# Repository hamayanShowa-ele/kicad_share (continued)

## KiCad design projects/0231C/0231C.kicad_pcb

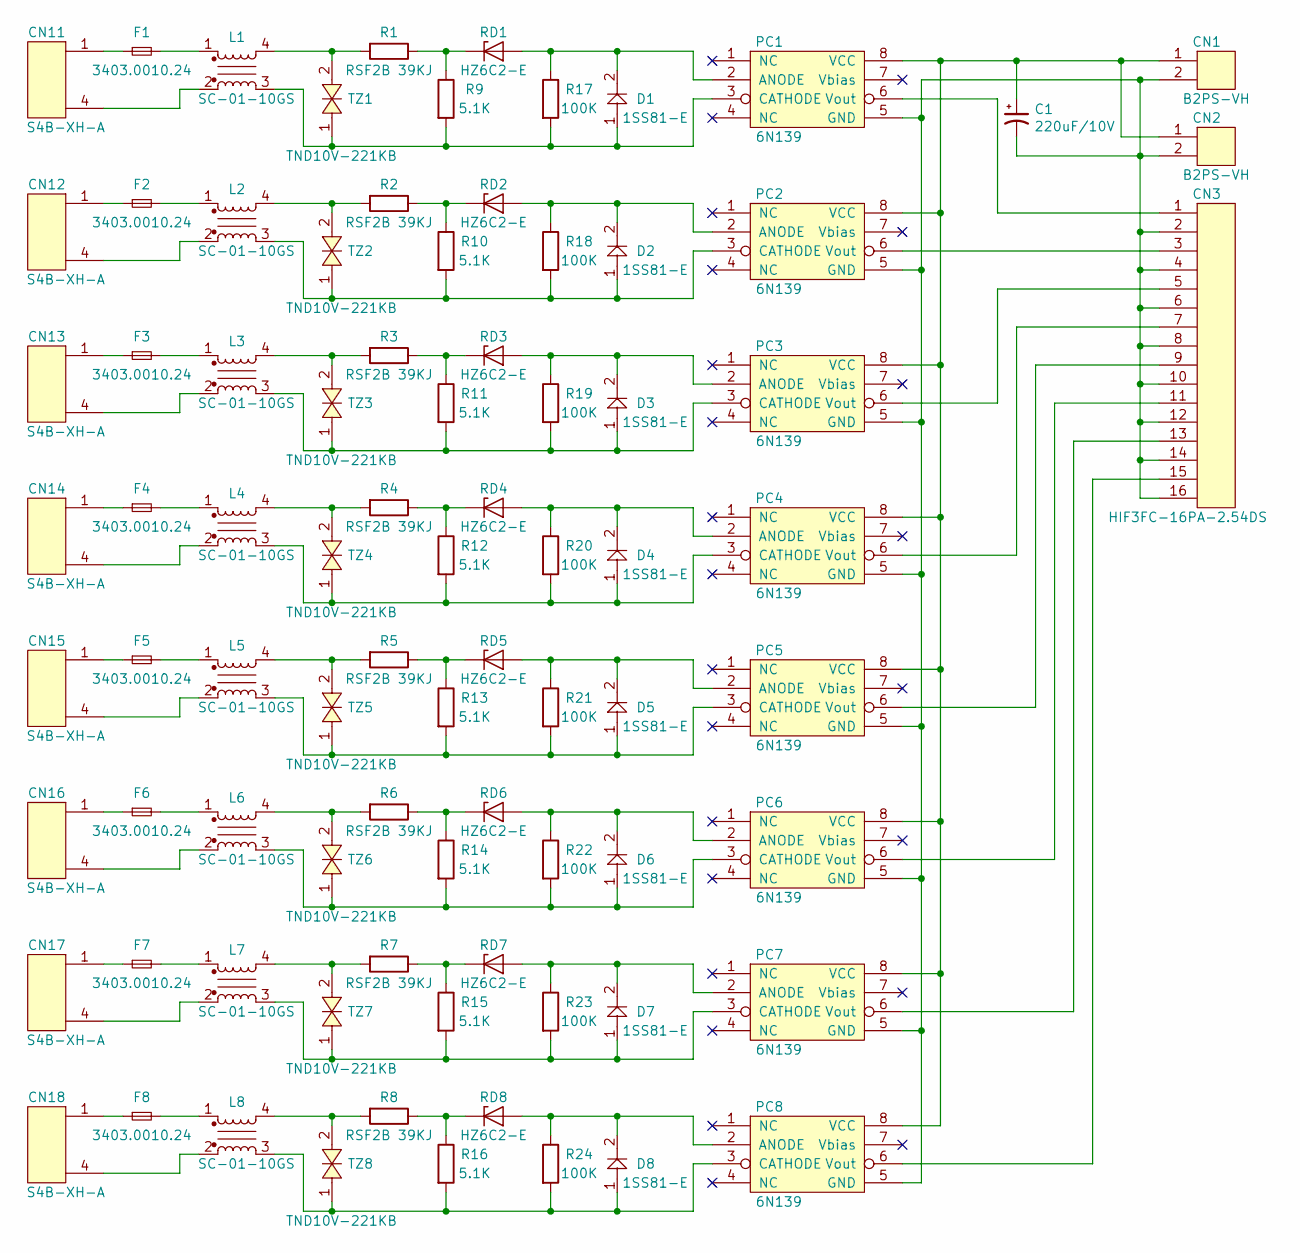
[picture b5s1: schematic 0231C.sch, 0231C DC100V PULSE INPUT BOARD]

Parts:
C1: 220uF/10V; CP_Radial_D8.00mm_P2.50mm
CN1, CN2: B2PS-VH; cn_B2PS-VH
CN3: HIF3FC-16PA-2.54DS; cn_HIF3FC-16PA-254DS
CN11, CN12, CN13, CN14, CN15, CN16, CN17, CN18: S4B-XH-A; cn_S4B-XH-A_KIRI_2-3
D1, D2, D3, D4, D5, D6, D7, D8: 1SS81-E; D_TH_10R16
F1, F2, F3, F4, F5, F6, F7, F8: 3403.0010.24; f_3403_0010_24
L1, L2, L3, L4, L5, L6, L7, L8: SC-01-10GS; l_SC-01-10GS
PC1, PC2, PC3, PC4, PC5, PC6, PC7, PC8: 6N139; ic_DIP-8_W7.62mm
R1, R2, R3, R4, R5, R6, R7, R8: RSF2B 39KJ; r_RSF2B
R9, R10, R11, R12, R13, R14, R15, R16: 5.1K; R_TH_10R16
R17, R18, R19, R20, R21, R22, R23, R24: 100K; R_TH_10R16
RD1, RD2, RD3, RD4, RD5, RD6, RD7, RD8: HZ6C2-E; RD_TH_10R16
TZ1, TZ2, TZ3, TZ4, TZ5, TZ6, TZ7, TZ8: TND10V-221KB; tvs_TND10V-221KB

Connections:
unnamed: C1.1, CN1.1, CN2.1, PC1.8 (VCC), PC2.8 (VCC), PC3.8 (VCC), PC4.8 (VCC), PC5.8 (VCC), PC6.8 (VCC), PC7.8 (VCC), PC8.8 (VCC)
unnamed: C1.2, CN1.2, CN2.2, CN3.2, CN3.4, CN3.6, CN3.8, CN3.10, CN3.12, CN3.14, CN3.16, PC1.5 (GND), PC2.5 (GND), PC3.5 (GND), PC4.5 (GND), PC5.5 (GND), PC6.5 (GND), PC7.5 (GND), PC8.5 (GND)
unnamed: CN3.1, PC1.6 (Vout)
unnamed: CN3.3, PC2.6 (Vout)
unnamed: CN3.5, PC3.6 (Vout)
unnamed: CN3.7, PC4.6 (Vout)
unnamed: CN3.9, PC5.6 (Vout)
unnamed: CN3.11, PC6.6 (Vout)
unnamed: CN3.13, PC7.6 (Vout)
unnamed: CN3.15, PC8.6 (Vout)
unnamed: CN11.1, F1.1
unnamed: CN11.4, L1.2
unnamed: CN12.1, F2.1
unnamed: CN12.4, L2.2
unnamed: CN13.1, F3.1
unnamed: CN13.4, L3.2
unnamed: CN14.1, F4.1
unnamed: CN14.4, L4.2
unnamed: CN15.1, F5.1
unnamed: CN15.4, L5.2
unnamed: CN16.1, F6.1
unnamed: CN16.4, L6.2
unnamed: CN17.1, F7.1
unnamed: CN17.4, L7.2
unnamed: CN18.1, F8.1
unnamed: CN18.4, L8.2
unnamed: D1.1, L1.3, PC1.3 (CATHODE), R9.2, R17.2, TZ1.1
unnamed: D1.2, PC1.2 (ANODE), R17.1, RD1.1 (A)
unnamed: D2.1, L2.3, PC2.3 (CATHODE), R10.2, R18.2, TZ2.1
unnamed: D2.2, PC2.2 (ANODE), R18.1, RD2.1 (A)
unnamed: D3.1, L3.3, PC3.3 (CATHODE), R11.2, R19.2, TZ3.1
unnamed: D3.2, PC3.2 (ANODE), R19.1, RD3.1 (A)
unnamed: D4.1, L4.3, PC4.3 (CATHODE), R12.2, R20.2, TZ4.1
unnamed: D4.2, PC4.2 (ANODE), R20.1, RD4.1 (A)
unnamed: D5.1, L5.3, PC5.3 (CATHODE), R13.2, R21.2, TZ5.1
unnamed: D5.2, PC5.2 (ANODE), R21.1, RD5.1 (A)
unnamed: D6.1, L6.3, PC6.3 (CATHODE), R14.2, R22.2, TZ6.1
unnamed: D6.2, PC6.2 (ANODE), R22.1, RD6.1 (A)
unnamed: D7.1, L7.3, PC7.3 (CATHODE), R15.2, R23.2, TZ7.1
unnamed: D7.2, PC7.2 (ANODE), R23.1, RD7.1 (A)
unnamed: D8.1, L8.3, PC8.3 (CATHODE), R16.2, R24.2, TZ8.1
unnamed: D8.2, PC8.2 (ANODE), R24.1, RD8.1 (A)
unnamed: F1.2, L1.1
unnamed: F2.2, L2.1
unnamed: F3.2, L3.1
unnamed: F4.2, L4.1
unnamed: F5.2, L5.1
unnamed: F6.2, L6.1
unnamed: F7.2, L7.1
unnamed: F8.2, L8.1
unnamed: L1.4, R1.2, TZ1.2
unnamed: L2.4, R2.2, TZ2.2
unnamed: L3.4, R3.2, TZ3.2
unnamed: L4.4, R4.2, TZ4.2
unnamed: L5.4, R5.2, TZ5.2
unnamed: L6.4, R6.2, TZ6.2
unnamed: L7.4, R7.2, TZ7.2
unnamed: L8.4, R8.2, TZ8.2
unnamed: R1.1, R9.1, RD1.2 (K)
unnamed: R2.1, R10.1, RD2.2 (K)
unnamed: R3.1, R11.1, RD3.2 (K)
unnamed: R4.1, R12.1, RD4.2 (K)
unnamed: R5.1, R13.1, RD5.2 (K)
unnamed: R6.1, R14.1, RD6.2 (K)
unnamed: R7.1, R15.1, RD7.2 (K)
unnamed: R8.1, R16.1, RD8.2 (K)

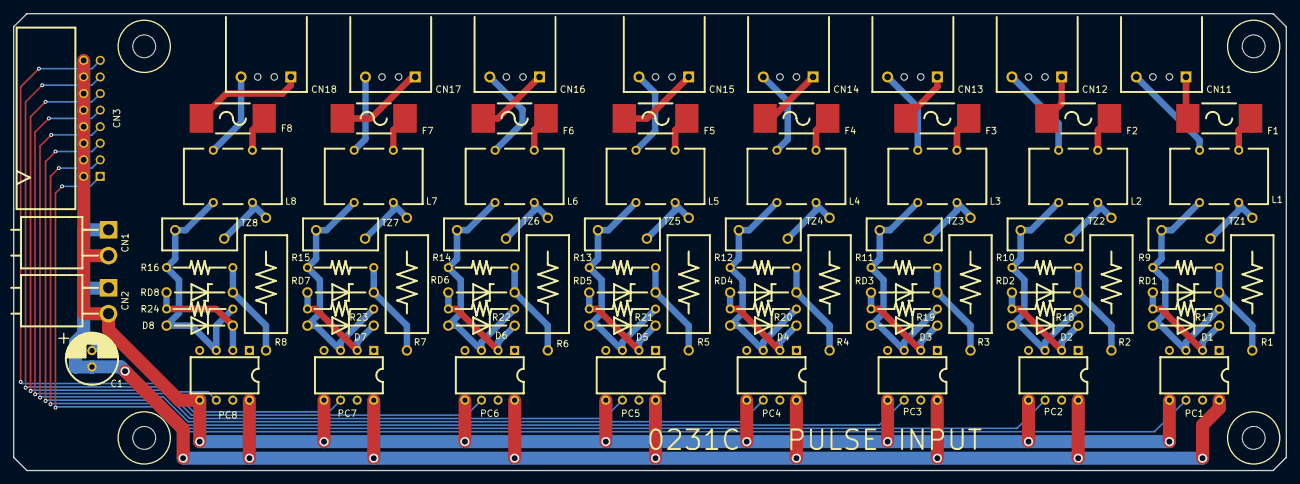
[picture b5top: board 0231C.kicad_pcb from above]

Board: 2 copper layers, 195.0 x 70.0 mm, 84 parts (0 on the bottom side), 66 nets.

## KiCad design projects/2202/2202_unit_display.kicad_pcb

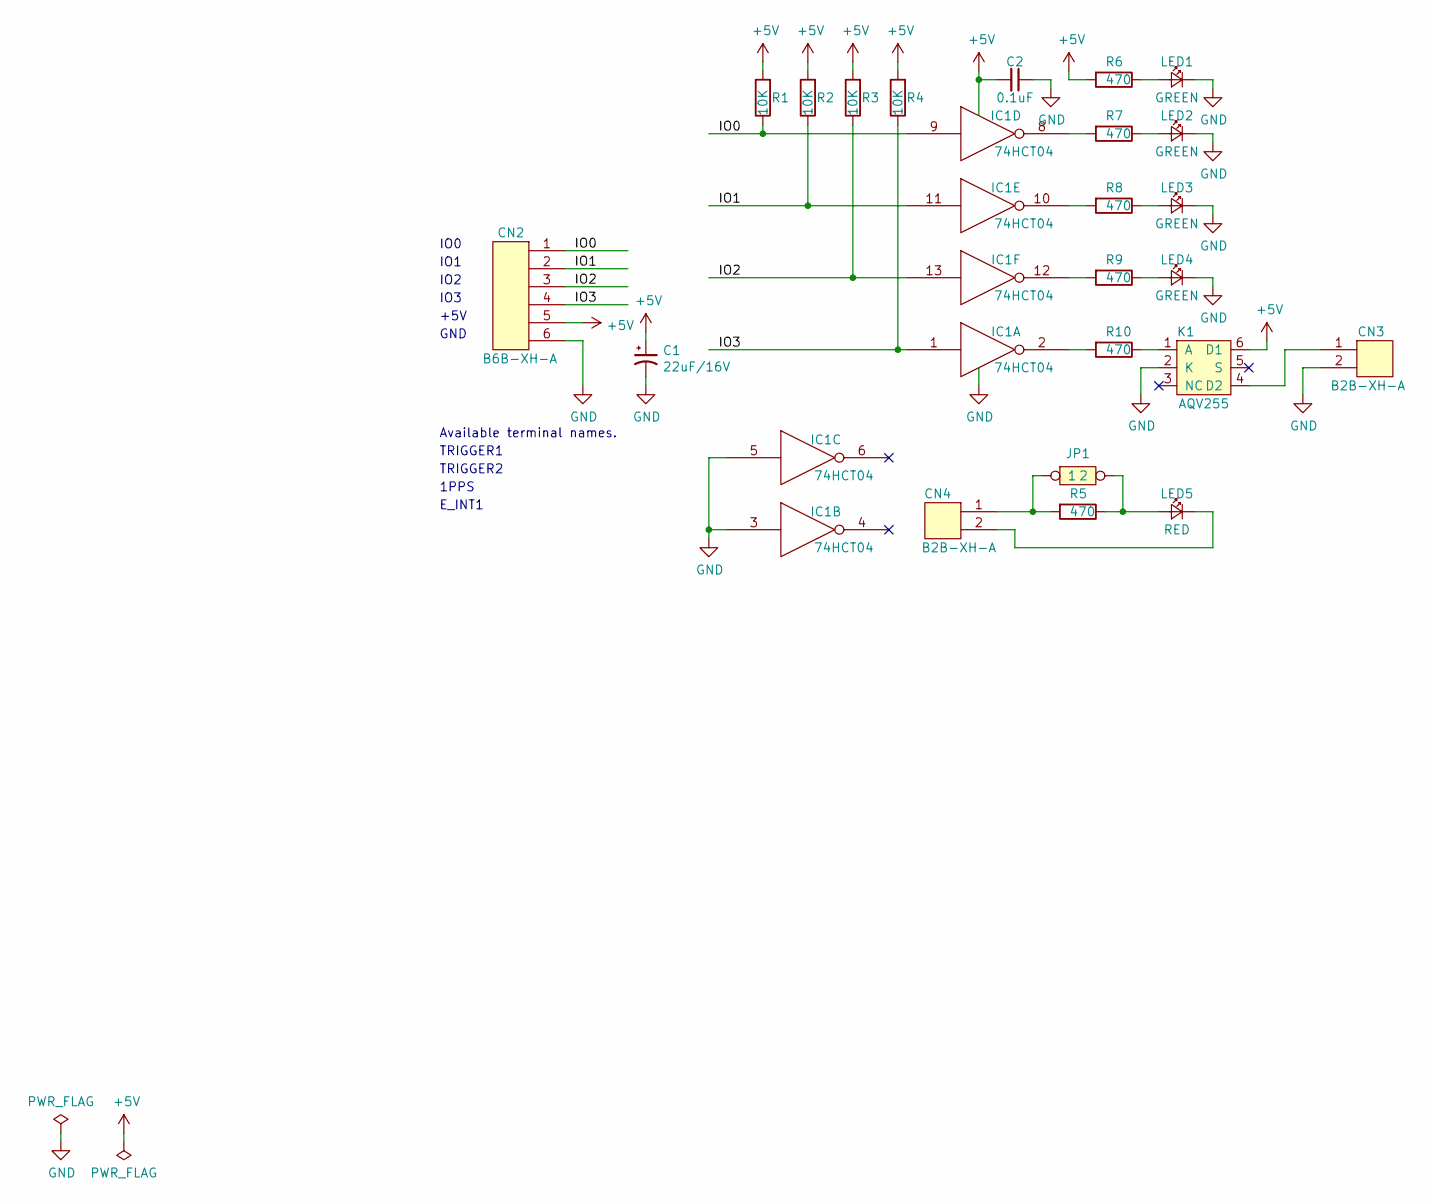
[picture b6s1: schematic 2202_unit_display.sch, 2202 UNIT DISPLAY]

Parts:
C1: 22uF/16V; CP_Radial_D5.0mm_P2.00mm
C2: 0.1uF; C_0603
CN2: B6B-XH-A; cn_B6B-XH-A
CN3, CN4: B2B-XH-A; cn_B2B-XH-A
IC1: 74HCT04; ic_DIP-14_W7.62mm
JP1: JUMPER2*1; JP_JUMPER1x2
K1: AQV255; ic_DIP-6_W7.62mm
LED1, LED2, LED3, LED4: GREEN; LED_D3.0mm_center
LED5: RED; LED_D3.0mm_center
R1, R2, R3, R4: 10K; R_TH_5R08
R5, R6, R7, R8, R9, R10: 470; R_TH_5R08

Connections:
+5V: C1.1, C2.2, CN2.5, IC1.14 (VCC), K1.6 (D1), R1.2, R2.2, R3.2, R4.2, R6.2
/IO0: CN2.1, IC1.9, R1.1
/IO1: CN2.2, IC1.11, R2.1
/IO2: CN2.3, IC1.13, R3.1
/IO3: CN2.4, IC1.1, R4.1
GND: C1.2, C2.1, CN2.6, CN3.2, IC1.3, IC1.5, IC1.7 (GNDA), K1.2 (K), LED1.2 (K), LED2.2 (K), LED3.2 (K), LED4.2 (K)
unnamed: CN3.1, K1.4 (D2)
unnamed: CN4.1, JP1.1, R5.2
unnamed: CN4.2, LED5.2 (K)
unnamed: IC1.2, R10.2
unnamed: IC1.8, R7.2
unnamed: IC1.10, R8.2
unnamed: IC1.12, R9.2
unnamed: JP1.2, LED5.1 (A), R5.1
unnamed: K1.1 (A), R10.1
unnamed: LED1.1 (A), R6.1
unnamed: LED2.1 (A), R7.1
unnamed: LED3.1 (A), R8.1
unnamed: LED4.1 (A), R9.1

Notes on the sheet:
TRIGGER1
TRIGGER2
1PPS
E_INT1
+5V
GND
IO0
IO1
IO2
IO3
Available terminal names.

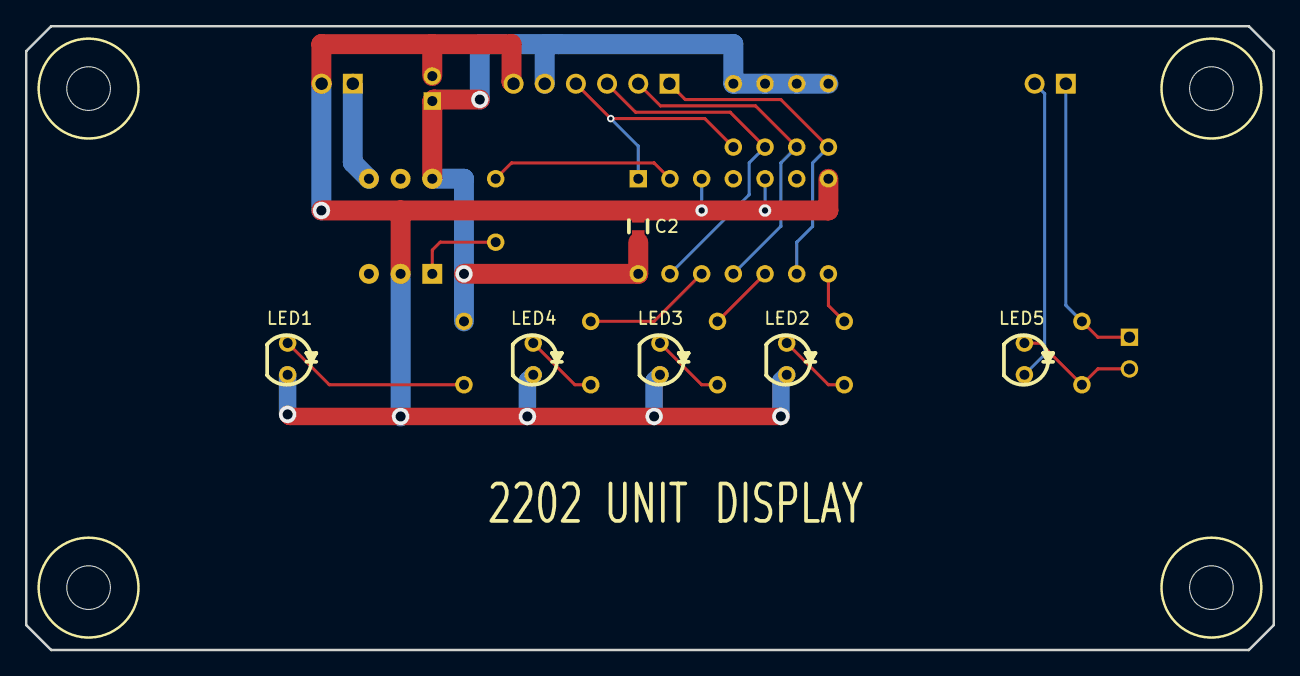
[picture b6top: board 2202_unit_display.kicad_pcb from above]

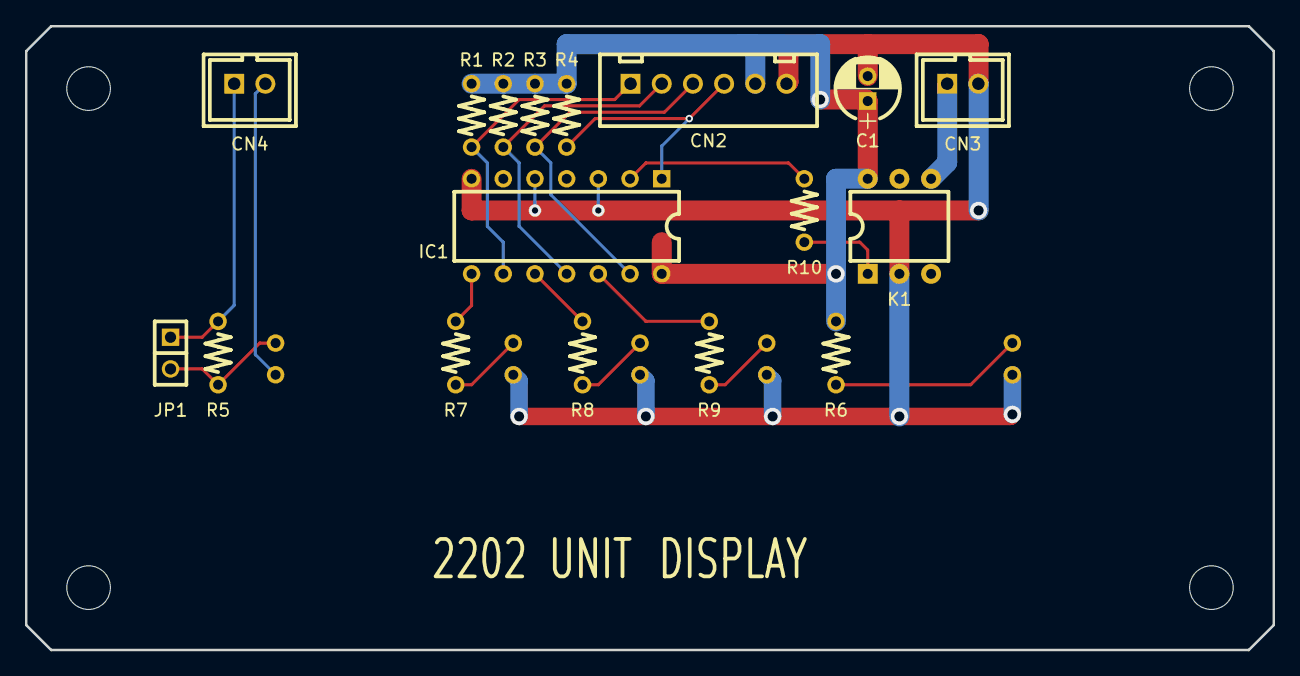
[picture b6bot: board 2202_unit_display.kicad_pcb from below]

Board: 2 copper layers, 100.0 x 50.0 mm, 23 parts (17 on the bottom side), 19 nets.

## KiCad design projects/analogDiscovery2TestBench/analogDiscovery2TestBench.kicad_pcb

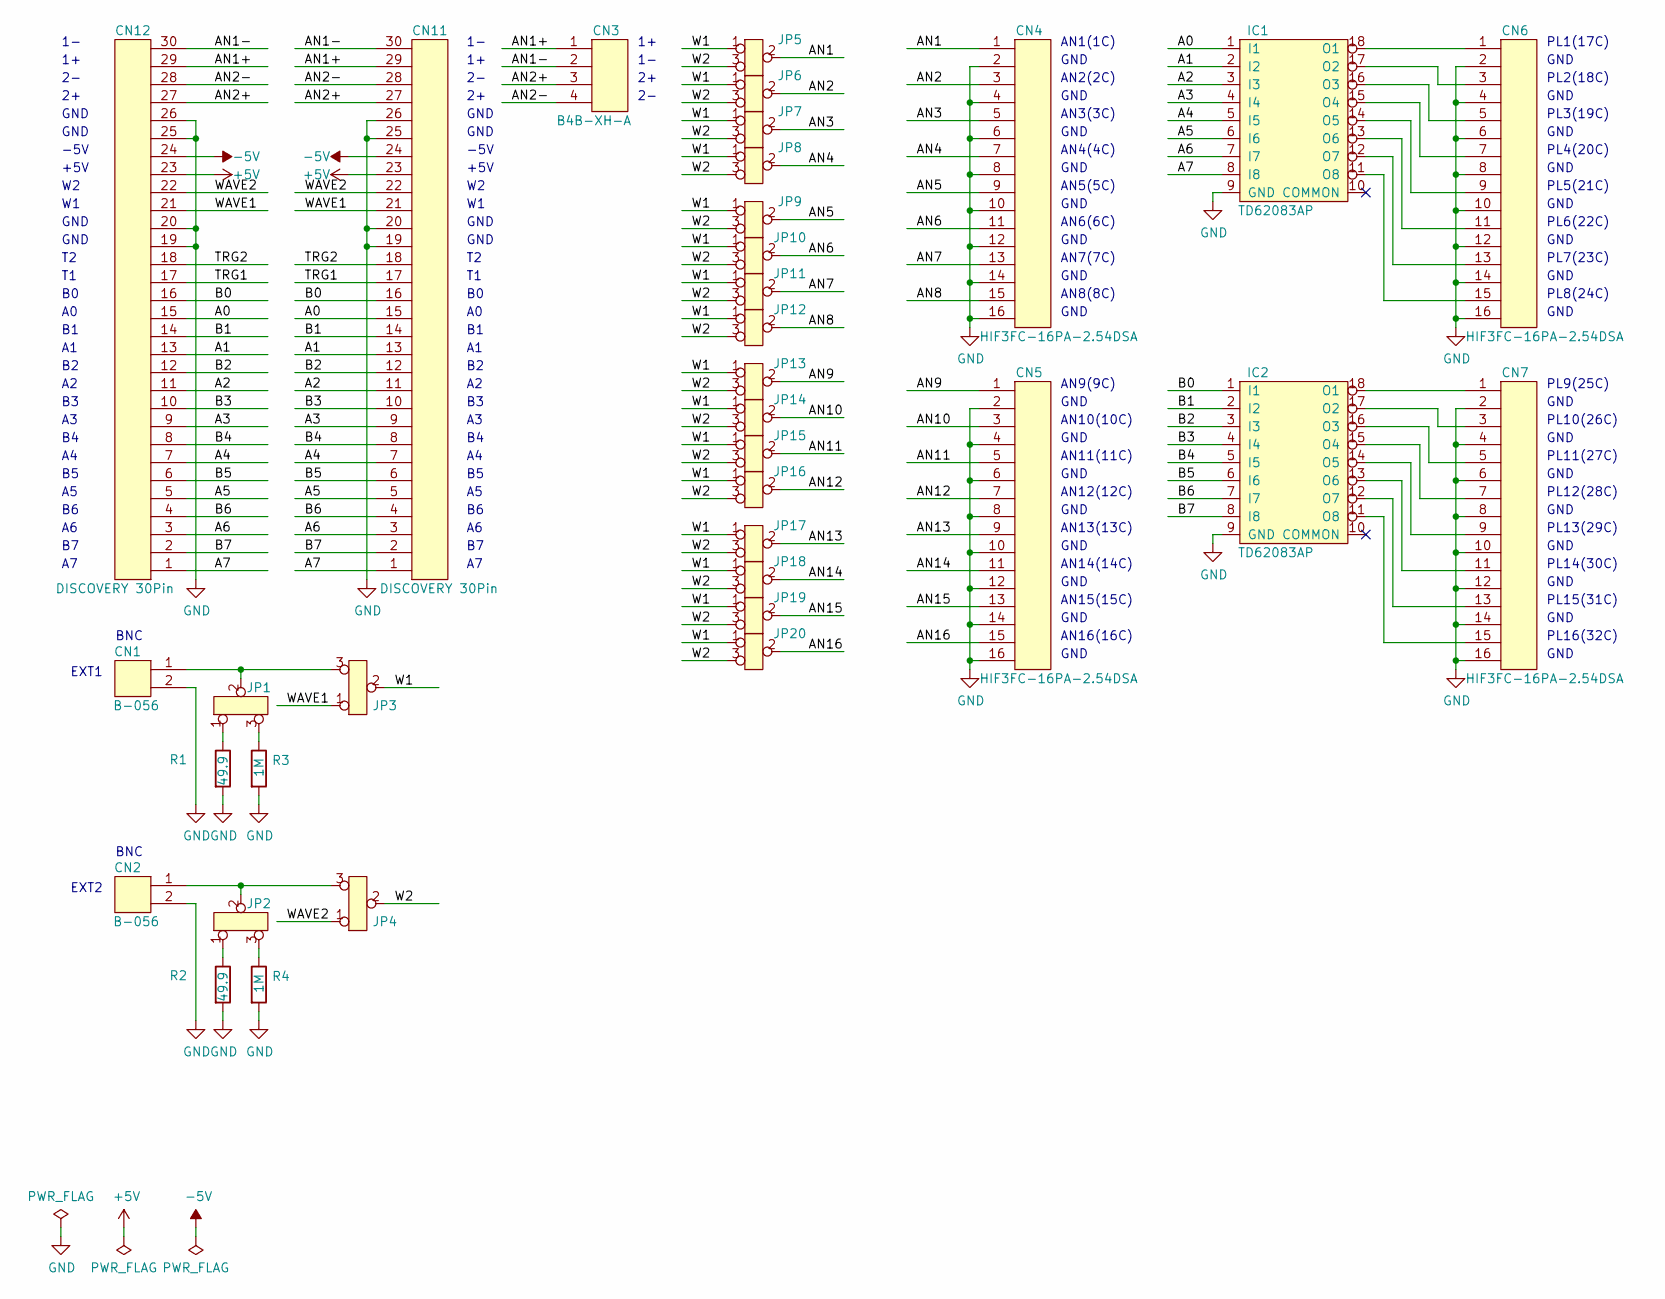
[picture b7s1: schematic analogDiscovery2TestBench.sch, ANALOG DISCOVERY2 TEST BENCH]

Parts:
CN1, CN2: B-056; cn_B-056
CN3: B4B-XH-A; cn_B4B-XH-A
CN4, CN5, CN6, CN7: HIF3FC-16PA-2.54DSA; cn_HIF3FC-16PA-254DSA
CN11, CN12: DISCOVERY 30Pin; cn_HIF3FC-30PA-254DSA
IC1, IC2: TD62083AP; ic_DIP-18_W7.62mm
JP1, JP2, JP3, JP4: JUMPER1*3; jp_JUMPER1_3
JP5, JP6, JP7, JP8, JP9, JP10, JP11, JP12, JP13, JP14, JP15, JP16, JP17, JP18, JP19, JP20: JUMPER1*3_SMALL; jp_JUMPER1_3
R1, R2: 49.9; R_TH_10R16
R3, R4: 1M; R_TH_10R16

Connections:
+5V: CN11.23, CN12.23
-5V: CN11.24, CN12.24
/A0: CN11.15, CN12.15, IC1.1 (I1)
/A1: CN11.13, CN12.13, IC1.2 (I2)
/A2: CN11.11, CN12.11, IC1.3 (I3)
/A3: CN11.9, CN12.9, IC1.4 (I4)
/A4: CN11.7, CN12.7, IC1.5 (I5)
/A5: CN11.5, CN12.5, IC1.6 (I6)
/A6: CN11.3, CN12.3, IC1.7 (I7)
/A7: CN11.1, CN12.1, IC1.8 (I8)
/AN1: CN4.1, JP5.2
/AN1+: CN3.1, CN11.29, CN12.29
/AN1-: CN3.2, CN11.30, CN12.30
/AN2: CN4.3, JP6.2
/AN2+: CN3.3, CN11.27, CN12.27
/AN2-: CN3.4, CN11.28, CN12.28
/AN3: CN4.5, JP7.2
/AN4: CN4.7, JP8.2
/AN5: CN4.9, JP9.2
/AN6: CN4.11, JP10.2
/AN7: CN4.13, JP11.2
/AN8: CN4.15, JP12.2
/AN9: CN5.1, JP13.2
/AN10: CN5.3, JP14.2
/AN11: CN5.5, JP15.2
/AN12: CN5.7, JP16.2
/AN13: CN5.9, JP17.2
/AN14: CN5.11, JP18.2
/AN15: CN5.13, JP19.2
/AN16: CN5.15, JP20.2
/B0: CN11.16, CN12.16, IC2.1 (I1)
/B1: CN11.14, CN12.14, IC2.2 (I2)
/B2: CN11.12, CN12.12, IC2.3 (I3)
/B3: CN11.10, CN12.10, IC2.4 (I4)
/B4: CN11.8, CN12.8, IC2.5 (I5)
/B5: CN11.6, CN12.6, IC2.6 (I6)
/B6: CN11.4, CN12.4, IC2.7 (I7)
/B7: CN11.2, CN12.2, IC2.8 (I8)
/TRG1: CN11.17, CN12.17
/TRG2: CN11.18, CN12.18
/W1: JP3.2, JP5.1, JP6.1, JP7.1, JP8.1, JP9.1, JP10.1, JP11.1, JP12.1, JP13.1, JP14.1, JP15.1, JP16.1, JP17.1, JP18.1, JP19.1, JP20.1
/W2: JP4.2, JP5.3, JP6.3, JP7.3, JP8.3, JP9.3, JP10.3, JP11.3, JP12.3, JP13.3, JP14.3, JP15.3, JP16.3, JP17.3, JP18.3, JP19.3, JP20.3
/WAVE1: CN11.21, CN12.21, JP3.1
/WAVE2: CN11.22, CN12.22, JP4.1
GND: CN1.2, CN2.2, CN4.2, CN4.4, CN4.6, CN4.8, CN4.10, CN4.12, CN4.14, CN4.16, CN5.2, CN5.4, CN5.6, CN5.8, CN5.10, CN5.12, CN5.14, CN5.16, CN6.2, CN6.4, CN6.6, CN6.8, CN6.10, CN6.12, CN6.14, CN6.16, CN7.2, CN7.4, CN7.6, CN7.8, CN7.10, CN7.12, CN7.14, CN7.16, CN11.19, CN11.20, CN11.25, CN11.26, CN12.19, CN12.20, CN12.25, CN12.26, IC1.9 (GND), IC2.9 (GND), R1.2, R2.2, R3.2, R4.2
unnamed: CN1.1, JP1.2, JP3.3
unnamed: CN2.1, JP2.2, JP4.3
unnamed: CN6.1, IC1.18 (O1)
unnamed: CN6.3, IC1.17 (O2)
unnamed: CN6.5, IC1.16 (O3)
unnamed: CN6.7, IC1.15 (O4)
unnamed: CN6.9, IC1.14 (O5)
unnamed: CN6.11, IC1.13 (O6)
unnamed: CN6.13, IC1.12 (O7)
unnamed: CN6.15, IC1.11 (O8)
unnamed: CN7.1, IC2.18 (O1)
unnamed: CN7.3, IC2.17 (O2)
unnamed: CN7.5, IC2.16 (O3)
unnamed: CN7.7, IC2.15 (O4)
unnamed: CN7.9, IC2.14 (O5)
unnamed: CN7.11, IC2.13 (O6)
unnamed: CN7.13, IC2.12 (O7)
unnamed: CN7.15, IC2.11 (O8)
unnamed: JP1.1, R1.1
unnamed: JP1.3, R3.1
unnamed: JP2.1, R2.1
unnamed: JP2.3, R4.1

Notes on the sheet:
-5V
+5V
GND
BNC
AN1(1C)
AN2(2C)
AN3(3C)
AN4(4C)
AN5(5C)
AN6(6C)
AN7(7C)
AN8(8C)
AN9(9C)
AN10(10C)
AN11(11C)
AN12(12C)
AN13(13C)
AN14(14C)
AN15(15C)
AN16(16C)
PL13(29C)
PL14(30C)
PL15(31C)
PL16(32C)
PL12(28C)
PL11(27C)
PL10(26C)
PL9(25C)
PL8(24C)
PL7(23C)
PL6(22C)
PL5(21C)
PL4(20C)
PL3(19C)
PL2(18C)
PL1(17C)
EXT1
EXT2

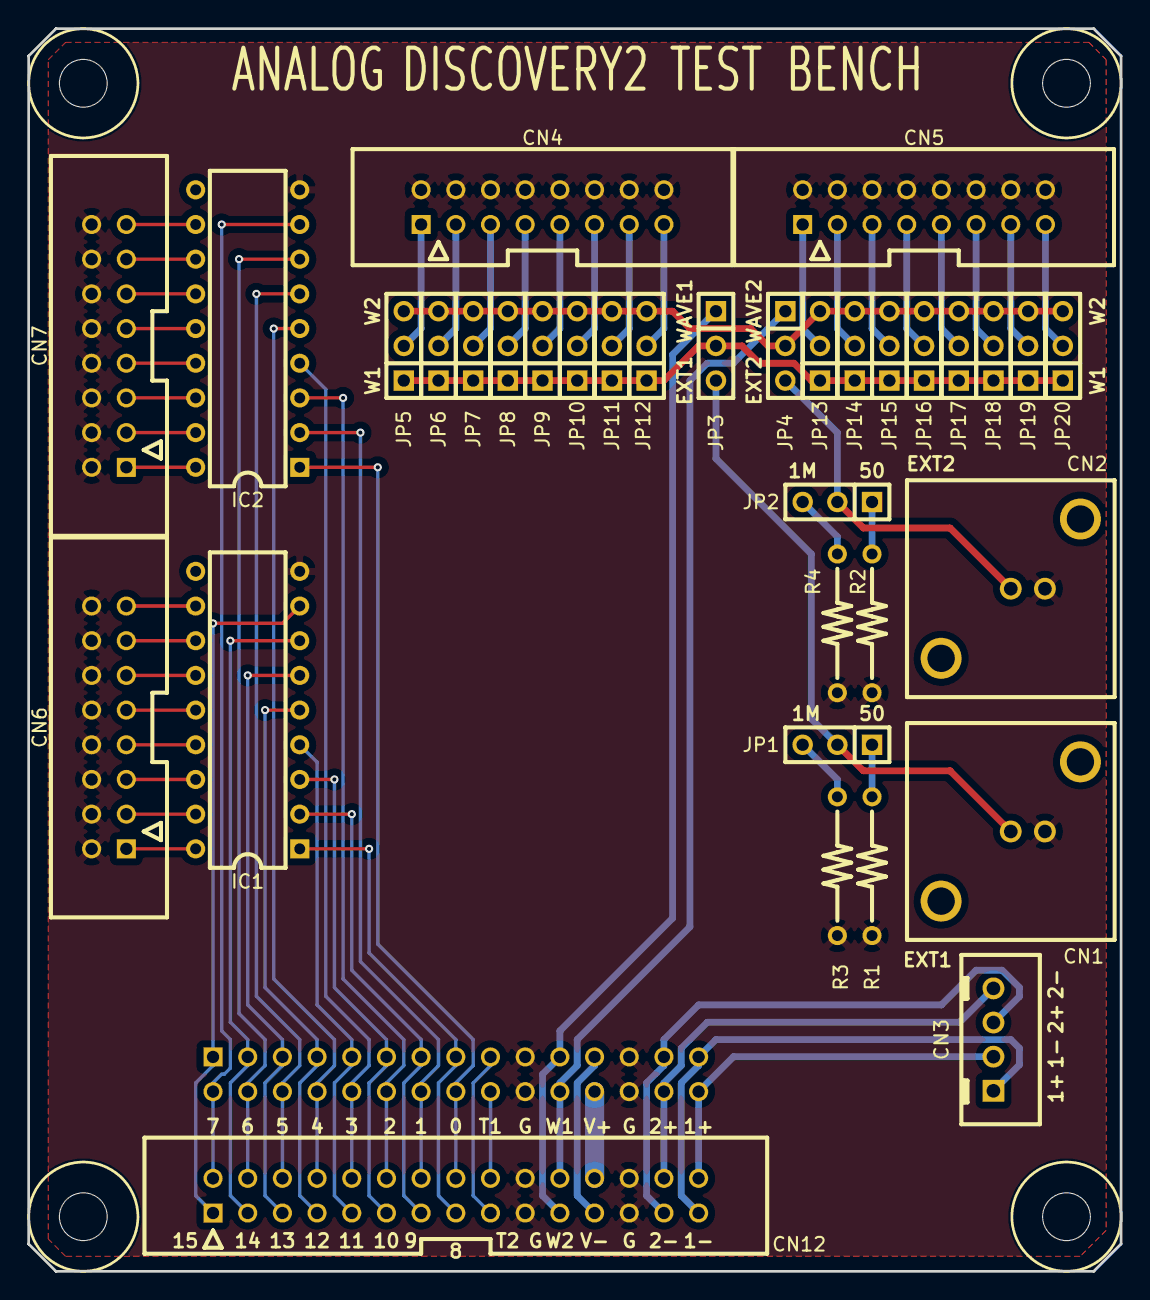
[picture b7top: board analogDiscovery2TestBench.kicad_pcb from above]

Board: 2 copper layers, 80.0 x 91.0 mm, 35 parts (1 on the bottom side), 67 nets.

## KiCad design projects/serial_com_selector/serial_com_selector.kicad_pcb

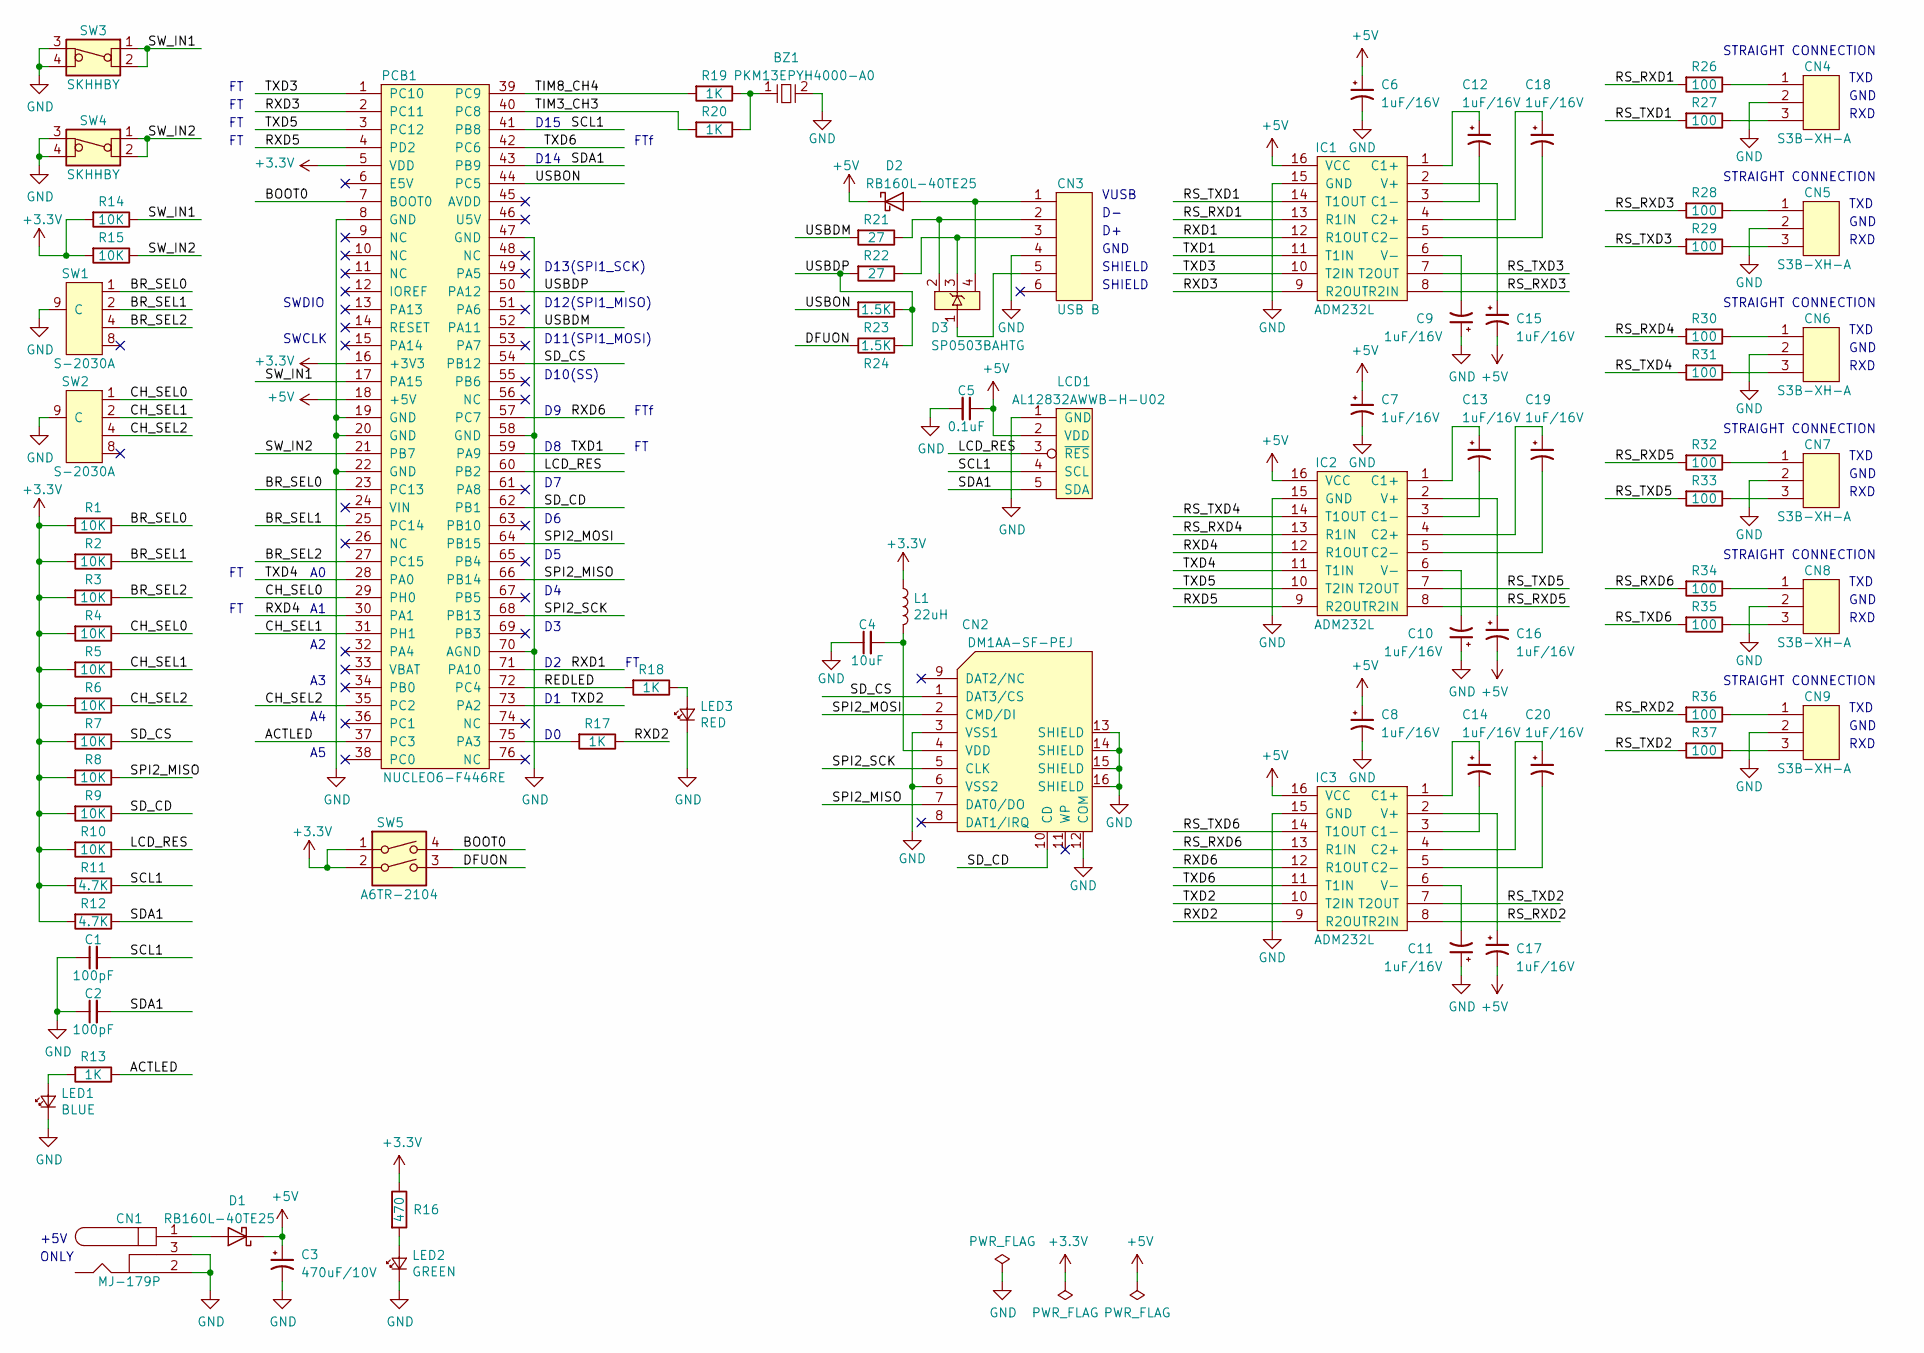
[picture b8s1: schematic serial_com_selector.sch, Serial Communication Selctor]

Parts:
BZ1: PKM13EPYH4000-A0; bz_PKM13EPYH4000-A0
C1, C2: 100pF; C_0603
C3: 470uF/10V; CP_Radial_D8.25mm_P3.80mm
C4: 10uF; C_0805
C5: 0.1uF; C_0603
C6, C7, C8, C9, C10, C11, C12, C13, C14, C15, C16, C17, C18, C19, C20: 1uF/16V; CP_Radial_D5.0mm_P2.00mm
CN1: MJ-179P; cn_MJ-179P
CN2: DM1AA-SF-PEJ; cn_HRS_DM1AA-SF-PEJ(21)
CN3: USB B; cn_USB_B
CN4, CN5, CN6, CN7, CN8, CN9: S3B-XH-A; cn_S3B-XH-A
D1, D2: RB160L-40TE25; d_SX34F
D3: SP0503BAHTG; d_SP0503BAHT
IC1, IC2, IC3: ADM232L; ic_DIP-16_W7.62mm
L1: 22uH; l_NR3010
LCD1: AL12832AWWB-H-U02; lcd_AL12832AWWB-H-U02
LED1: BLUE; C_0603
LED2: GREEN; C_0603
LED3: RED; C_0603
PCB1: NUCLEO6-F446RE; pcb_Nucleo_Extension_001
R1, R2, R3, R4, R5, R6, R7, R8, R9, R10, R14, R15: 10K; C_0603
R11, R12: 4.7K; C_0603
R13, R17, R18, R19, R20: 1K; C_0603
R16: 470; C_0603
R21, R22: 27; C_0603
R23, R24: 1.5K; C_0603
R26, R27, R28, R29, R30, R31, R32, R33, R34, R35, R36, R37: 100; C_0603
SW1, SW2: S-2030A; sw_S-2030A
SW3, SW4: SKHHBY; sw_SKHHBY
SW5: A6TR-2104; sw_A6TR-2104

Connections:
+3V3: L1.1, PCB1.5 (VDD), PCB1.16 (+3V3), R1.2, R2.2, R3.2, R4.2, R5.2, R6.2, R7.2, R8.2, R9.2, R10.2, R11.2, R12.2, R14.2, R15.2, R16.1, SW5.1, SW5.2
+5V: C3.1, C5.1, C6.1, C7.1, C8.1, C15.2, C16.2, C17.2, D1.2 (K), D2.2 (K), IC1.16 (VCC), IC2.16 (VCC), IC3.16 (VCC), LCD1.2 (VDD), PCB1.18 (+5V)
/ACTLED: PCB1.37 (PC3), R13.1
/BOOT0: PCB1.7 (BOOT0), SW5.4
/BR_SEL0: PCB1.23 (PC13), R1.1, SW1.1
/BR_SEL1: PCB1.25 (PC14), R2.1, SW1.2
/BR_SEL2: PCB1.27 (PC15), R3.1, SW1.4
/CH_SEL0: PCB1.29 (PH0), R4.1, SW2.1
/CH_SEL1: PCB1.31 (PH1), R5.1, SW2.2
/CH_SEL2: PCB1.35 (PC2), R6.1, SW2.4
/DFUON: R24.1, SW5.3
/LCD_RES: LCD1.3 (~RES), PCB1.60 (PB2), R10.1
/REDLED: PCB1.72 (PC4), R18.2
/RS_RXD1: IC1.13 (R1IN), R26.2
/RS_RXD2: IC3.8 (R2IN), R36.2
/RS_RXD3: IC1.8 (R2IN), R28.2
/RS_RXD4: IC2.13 (R1IN), R30.2
/RS_RXD5: IC2.8 (R2IN), R32.2
/RS_RXD6: IC3.13 (R1IN), R34.2
/RS_TXD1: IC1.14 (T1OUT), R27.2
/RS_TXD2: IC3.7 (T2OUT), R37.2
/RS_TXD3: IC1.7 (T2OUT), R29.2
/RS_TXD4: IC2.14 (T1OUT), R31.2
/RS_TXD5: IC2.7 (T2OUT), R33.2
/RS_TXD6: IC3.14 (T1OUT), R35.2
/RXD1: IC1.12 (R1OUT), PCB1.71 (PA10)
/RXD2: IC3.9 (R2OUT), R17.1
/RXD3: IC1.9 (R2OUT), PCB1.2 (PC11)
/RXD4: IC2.12 (R1OUT), PCB1.30 (PA1)
/RXD5: IC2.9 (R2OUT), PCB1.4 (PD2)
/RXD6: IC3.12 (R1OUT), PCB1.57 (PC7)
/SCL1: C1.2, LCD1.4 (SCL), PCB1.41 (PB8), R11.1
/SDA1: C2.2, LCD1.5 (SDA), PCB1.43 (PB9), R12.1
/SD_CD: CN2.10 (CD), PCB1.62 (PB1), R9.1
/SD_CS: CN2.1 (DAT3/CS), PCB1.54 (PB12), R7.1
/SPI2_MISO: CN2.7 (DAT0/DO), PCB1.66 (PB14), R8.1
/SPI2_MOSI: CN2.2 (CMD/DI), PCB1.64 (PB15)
/SPI2_SCK: CN2.5 (CLK), PCB1.68 (PB13)
/SW_IN1: PCB1.17 (PA15), R14.1, SW3.1, SW3.2
/SW_IN2: PCB1.21 (PB7), R15.1, SW4.1, SW4.2
/TIM3_CH3: PCB1.40 (PC8), R20.2
/TIM8_CH4: PCB1.39 (PC9), R19.2
/TXD1: IC1.11 (T1IN), PCB1.59 (PA9)
/TXD2: IC3.10 (T2IN), PCB1.73 (PA2)
/TXD3: IC1.10 (T2IN), PCB1.1 (PC10)
/TXD4: IC2.11 (T1IN), PCB1.28 (PA0)
/TXD5: IC2.10 (T2IN), PCB1.3 (PC12)
/TXD6: IC3.11 (T1IN), PCB1.42 (PC6)
/USBDM: PCB1.52 (PA11), R21.2
/USBDP: PCB1.50 (PA12), R22.2, R23.1, R24.2
/USBON: PCB1.44 (PC5), R23.2
GND: BZ1.2, C1.1, C2.1, C3.2, C4.1, C5.2, C6.2, C7.2, C8.2, C9.1, C10.1, C11.1, CN1.2, CN1.3, CN2.3 (VSS1), CN2.6 (VSS2), CN2.12 (COM), CN2.13 (SHIELD), CN2.14 (SHIELD), CN2.15 (SHIELD), CN2.16 (SHIELD), CN3.4, CN4.2, CN5.2, CN6.2, CN7.2, CN8.2, CN9.2, IC1.15 (GND), IC2.15 (GND), IC3.15 (GND), LCD1.1 (GND), LED1.2 (K), LED2.2 (K), LED3.2 (K), PCB1.8 (GND), PCB1.19 (GND), PCB1.20 (GND), PCB1.22 (GND), PCB1.47 (GND), PCB1.58 (GND), PCB1.70 (AGND), SW1.9 (C), SW2.9 (C), SW3.3, SW3.4, SW4.3, SW4.4
unnamed: BZ1.1, R19.1, R20.1
unnamed: C4.2, CN2.4 (VDD), L1.2
unnamed: C9.2, IC1.6 (V-)
unnamed: C10.2, IC2.6 (V-)
unnamed: C11.2, IC3.6 (V-)
unnamed: C12.1, IC1.1 (C1+)
unnamed: C12.2, IC1.3 (C1-)
unnamed: C13.1, IC2.1 (C1+)
unnamed: C13.2, IC2.3 (C1-)
unnamed: C14.1, IC3.1 (C1+)
unnamed: C14.2, IC3.3 (C1-)
unnamed: C15.1, IC1.2 (V+)
unnamed: C16.1, IC2.2 (V+)
unnamed: C17.1, IC3.2 (V+)
unnamed: C18.1, IC1.4 (C2+)
unnamed: C18.2, IC1.5 (C2-)
unnamed: C19.1, IC2.4 (C2+)
unnamed: C19.2, IC2.5 (C2-)
unnamed: C20.1, IC3.4 (C2+)
unnamed: C20.2, IC3.5 (C2-)
unnamed: CN1.1, D1.1 (A)
unnamed: CN3.1, D2.1 (A), D3.4
unnamed: CN3.2, D3.2, R21.1
unnamed: CN3.3, D3.3, R22.1
unnamed: CN3.5, D3.1
unnamed: CN4.1, R26.1
unnamed: CN4.3, R27.1
unnamed: CN5.1, R28.1
unnamed: CN5.3, R29.1
unnamed: CN6.1, R30.1
unnamed: CN6.3, R31.1
unnamed: CN7.1, R32.1
unnamed: CN7.3, R33.1
unnamed: CN8.1, R34.1
unnamed: CN8.3, R35.1
unnamed: CN9.1, R36.1
unnamed: CN9.3, R37.1
unnamed: LED1.1 (A), R13.2
unnamed: LED2.1 (A), R16.2
unnamed: LED3.1 (A), R18.1
unnamed: PCB1.75 (PA3), R17.2

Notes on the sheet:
D13(SPI1_SCK)
D12(SPI1_MISO)
D11(SPI1_MOSI)
D10(SS)
D15
D14
TXD
GND
RXD
STRAIGHT CONNECTION
SWDIO
SWCLK
FTf
VUSB
SHIELD
+5V
ONLY
